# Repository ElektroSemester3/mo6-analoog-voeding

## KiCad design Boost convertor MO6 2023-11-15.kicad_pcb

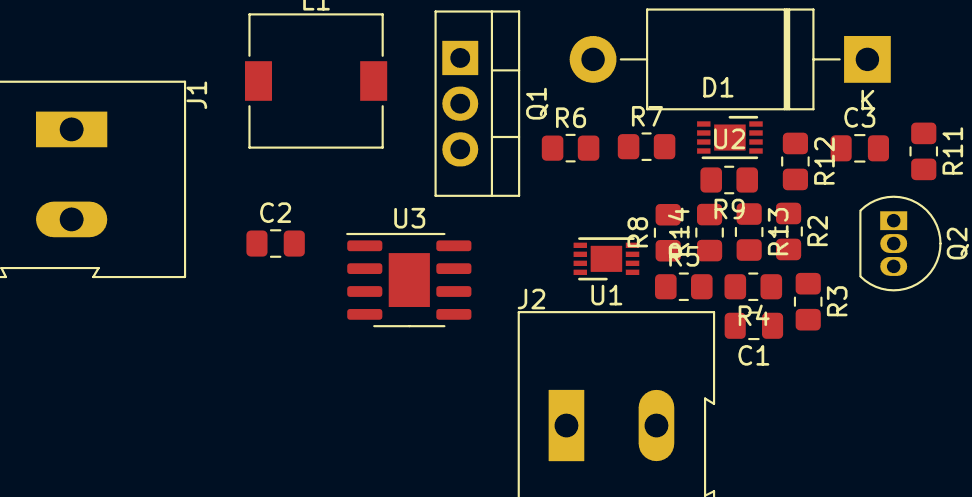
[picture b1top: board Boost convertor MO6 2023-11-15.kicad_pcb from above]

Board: 2 copper layers, 24 parts (0 on the bottom side), 18 nets, no tracks yet.

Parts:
C1: 47uF; C_0805_2012Metric_Pad1.18x1.45mm_HandSolder
C2: 10uF; C_0805_2012Metric_Pad1.18x1.45mm_HandSolder
C3: 100uF; C_0805_2012Metric_Pad1.18x1.45mm_HandSolder
D1: 1.5KExxA; D_DO-201AE_P15.24mm_Horizontal
J1, J2: Screw_Terminal_01x02; TerminalBlock_Altech_AK300-2_P5.00mm
L1: 10uH; L_7.3x7.3_H4.5
Q1: IRLZ44N; TO-220-3_Vertical
Q2: BC547; TO-92_Inline
R2, R3, R6, R8, R9, R14: 1k; R_0805_2012Metric_Pad1.20x1.40mm_HandSolder
R4: 10k; R_0805_2012Metric_Pad1.20x1.40mm_HandSolder
R5: 100K; R_0805_2012Metric_Pad1.20x1.40mm_HandSolder
R7: 19k; R_0805_2012Metric_Pad1.20x1.40mm_HandSolder
R11: 1.2k; R_0805_2012Metric_Pad1.20x1.40mm_HandSolder
R12: 33; R_0805_2012Metric_Pad1.20x1.40mm_HandSolder
R13: 820; R_0805_2012Metric_Pad1.20x1.40mm_HandSolder
U1, U2: MCP6002-xMC; DFN-8-1EP_3x2mm_P0.5mm_EP1.75x1.45mm
U3: L7805; SOIC-8-1EP_3.9x4.9mm_P1.27mm_EP2.29x3mm

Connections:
+5V: U1.3 (+), U2.8 (V+), U3.3 (OUT)
GND: C2.1, C3.1, J2.1, Q1.3 (S), Q2.3 (E), R3.2, R7.2, R9.2, R13.2, U1.4 (V-), U1.9 (V-), U2.4 (V-), U2.9 (V-), U3.2 (GND)
unnamed: C1.2, R5.1, R14.1, U1.1
unnamed: C3.2, D1.1 (A1), R2.1
unnamed: D1.2 (A2), L1.2, Q1.2 (D)
unnamed: C2.2, J1.1
unnamed: Q2.2 (B), R12.2
unnamed: R2.2, R3.1, R4.1
unnamed: R6.1, R8.1, U1.7
unnamed: R12.1, U2.7
unnamed: C1.1, R4.2, R5.2, U1.2 (-)
unnamed: R13.1, R14.2, U1.6 (-)
unnamed: R6.2, R7.1, U2.2 (-)
unnamed: R8.2, R9.1, U2.5 (+)
unnamed: U2.1, U2.6 (-)
PWM: Q1.1 (G), Q2.1 (C), R11.2
Vin: J1.2, L1.1, R11.1, U1.8 (V+), U3.1 (IN)
Zaagtand: J2.2, U1.5 (+), U2.3 (+)

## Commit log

2023-11-15 Schematic Boost convertor
2023-11-23 load verwijderd
    Ik heb de load verwijdert, want daar komt het systeem van de controllers aan te hangen.
    Verder heb ik C2 parallel gezet aan J1. Dit kan ik eerst in serie, maar dat was niet mijn bedoeling.
